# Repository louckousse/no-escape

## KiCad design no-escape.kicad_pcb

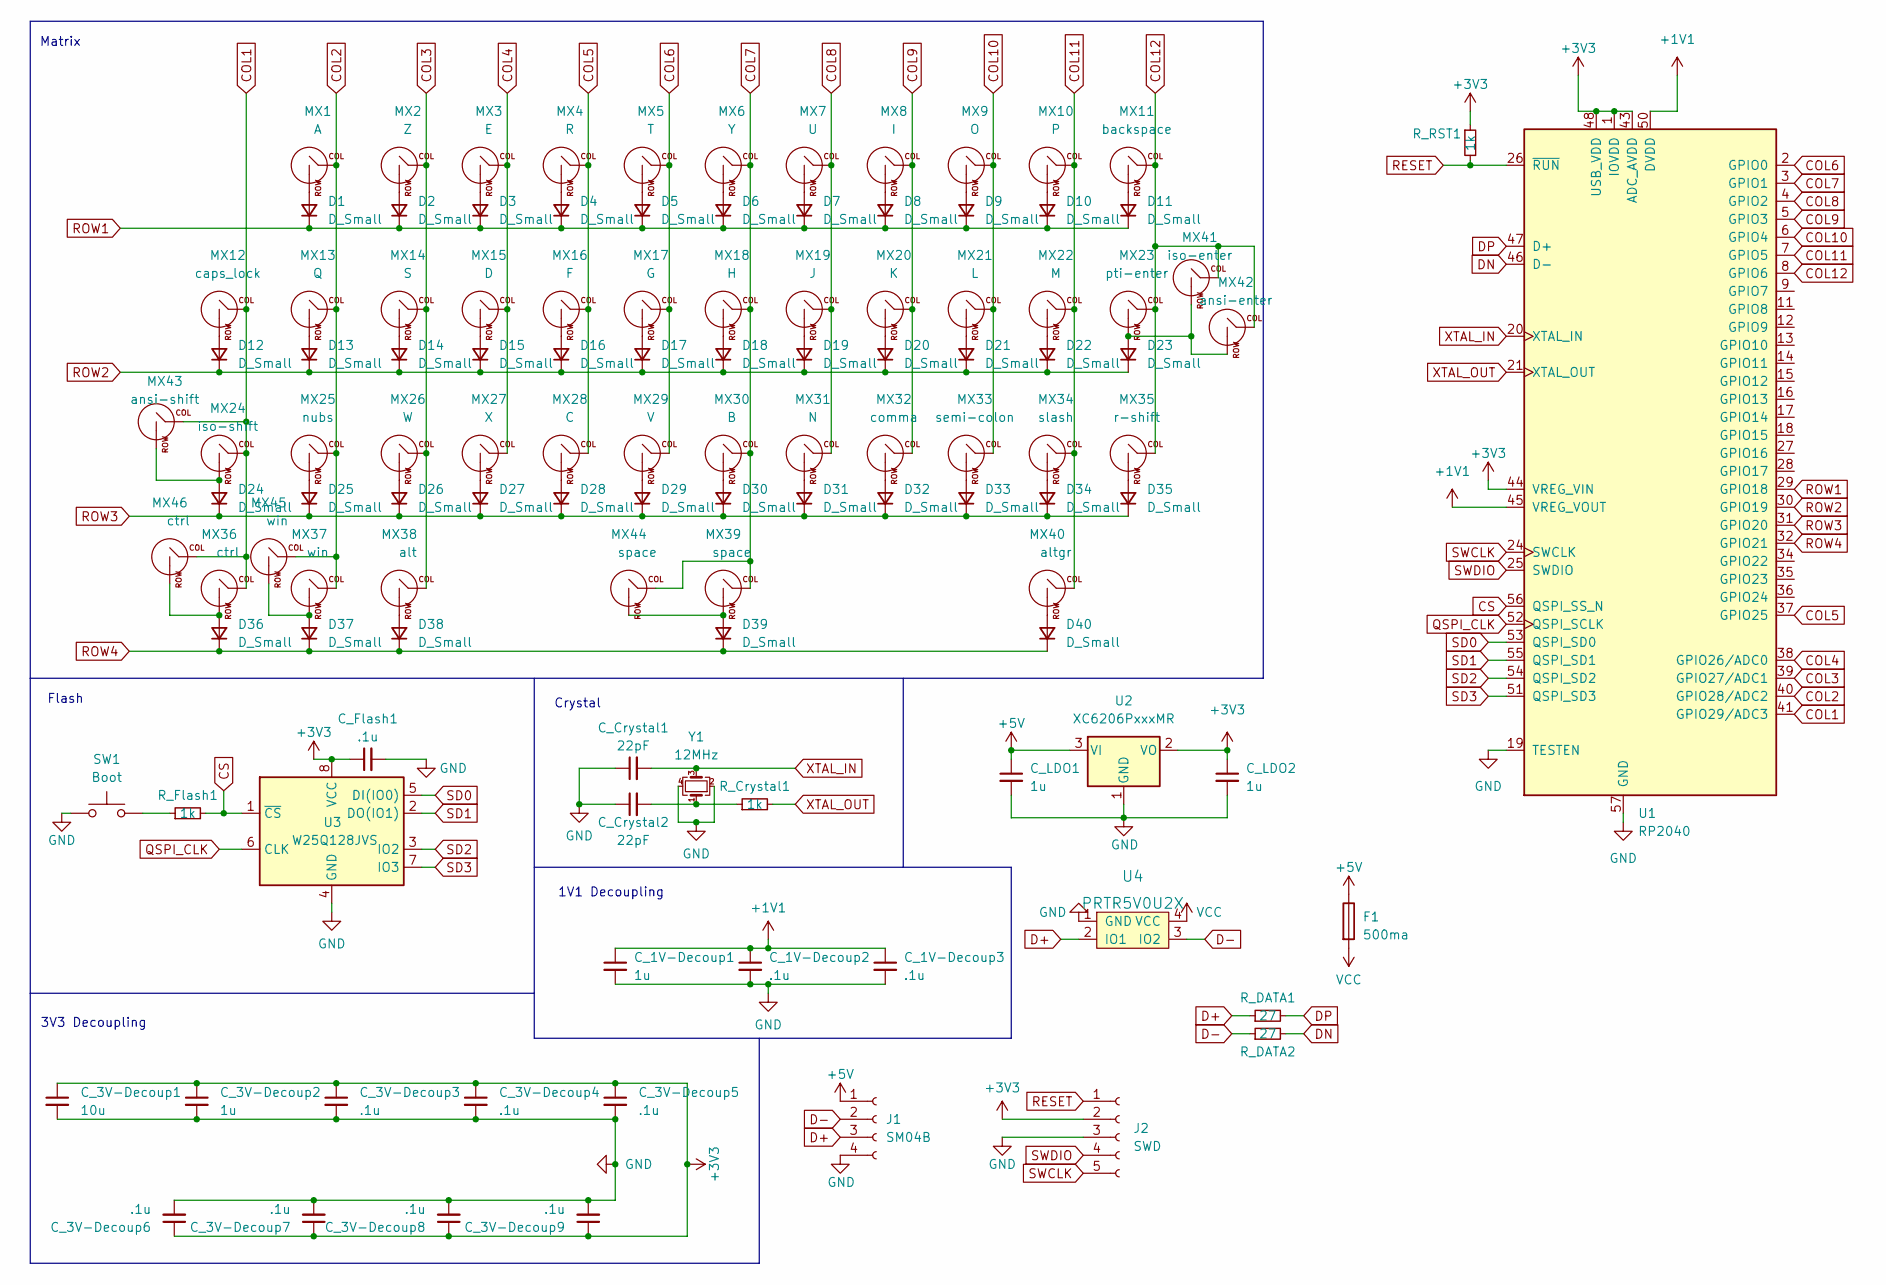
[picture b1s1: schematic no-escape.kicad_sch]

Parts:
C_1V-Decoup1, C_3V-Decoup2: 1u; C_0402_1005Metric
C_1V-Decoup2, C_1V-Decoup3, C_3V-Decoup3, C_3V-Decoup4, C_3V-Decoup5, C_3V-Decoup6, C_3V-Decoup7, C_3V-Decoup8, C_3V-Decoup9: .1u; C_0402_1005Metric
C_3V-Decoup1: 10u; C_0402_1005Metric
C_Crystal1, C_Crystal2: 22pF; C_0402_1005Metric
C_Flash1: .1u; C_0402_1005Metric
C_LDO1, C_LDO2: 1u; C_0402_1005Metric
D1, D2, D3, D4, D5, D6, D7, D8, D9, D10, D11, D12, D13, D14, D15, D16, D17, D18, D19, D20, D21, D22, D23, D24, D25, D26, D27, D28, D29, D30, D31, D32, D33, D34, D35, D36, D37, D38, D39, D40: D_Small; D_SOD-123
F1: 500ma; Fuse_0805_2012Metric
J1: SM04B; Molex_Pico-EZmate_78171-0004_1x04-1MP_P1.20mm_Vertical
J2: SWD; PinHeader_1x05_P2.54mm_Vertical
MX1: A; mx_1u
MX2: Z; mx_1u
MX3: E; mx_1u
MX4: R; mx_1u
MX5: T; mx_1u
MX6: Y; mx_1u
MX7: U; mx_1u
MX8: I; mx_1u
MX9: O; mx_1u
MX10: P; mx_1u
MX11: backspace; mx_15u
MX12: caps_lock; mx_stepped_caps
MX13: Q; mx_1u
MX14: S; mx_1u
MX15: D; mx_1u
MX16: F; mx_1u
MX17: G; mx_1u
MX18: H; mx_1u
MX19: J; mx_1u
MX20: K; mx_1u
MX21: L; mx_1u
MX22: M; mx_1u
MX23: pti-enter; mx_125u
MX24: iso-shift; mx_125u
MX25: nubs; mx_1u
MX26: W; mx_1u
MX27: X; mx_1u
MX28: C; mx_1u
MX29: V; mx_1u
MX30: B; mx_1u
MX31: N; mx_1u
MX32: comma; mx_1u
MX33: semi-colon; mx_1u
MX34: slash; mx_1u
MX35: r-shift; mx_175u
MX36: ctrl; mx_125u
MX37: win; mx_125u
MX38: alt; mx_1u
MX39: space; mx_7u
MX40: altgr; mx_1u
MX41: iso-enter; mx_iso
MX42: ansi-enter; mx_225u
MX43: ansi-shift; mx_225u
MX44: space; MX-Solderable-8U-ReversedStabilizers
MX45: win; mx_1u
MX46: ctrl; mx_15u
R_Crystal1: 1k; R_0402_1005Metric
R_DATA1, R_DATA2: 27; R_0402_1005Metric
R_Flash1: 1k; R_0402_1005Metric
R_RST1: 1k; R_0402_1005Metric
SW1: Boot; PinHeader_1x02_P2.54mm_Vertical
U1: RP2040; RP2040-QFN-56
U2: XC6206PxxxMR; SOT-23
U3: W25Q128JVS; SOIC-8_5.23x5.23mm_P1.27mm
U4: PRTR5V0U2X; SOT143B
Y1: 12MHz; Crystal_SMD_3225-4Pin_3.2x2.5mm

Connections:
+1V1: C_1V-Decoup1.1, C_1V-Decoup2.1, C_1V-Decoup3.1, U1.23 (DVDD), U1.45 (VREG_VOUT), U1.50 (DVDD)
+3V3: C_3V-Decoup1.1, C_3V-Decoup2.1, C_3V-Decoup3.1, C_3V-Decoup4.1, C_3V-Decoup5.1, C_3V-Decoup6.1, C_3V-Decoup7.1, C_3V-Decoup8.1, C_3V-Decoup9.1, C_Flash1.1, C_LDO2.1, J2.2, R_RST1.1, U1.1 (IOVDD), U1.10 (IOVDD), U1.22 (IOVDD), U1.33 (IOVDD), U1.42 (IOVDD), U1.43 (ADC_AVDD), U1.44 (VREG_VIN), U1.48 (USB_VDD), U1.49 (IOVDD), U2.2 (VO), U3.8 (VCC)
+5V: C_LDO1.1, F1.1, J1.1, U2.3 (VI)
COL1: MX12.1 (Passive), MX24.1 (Passive), MX36.1 (Passive), MX43.1 (Passive), MX46.1 (Passive), U1.41 (GPIO29/ADC3)
COL2: MX1.1 (Passive), MX13.1 (Passive), MX25.1 (Passive), MX37.1 (Passive), MX45.1 (Passive), U1.40 (GPIO28/ADC2)
COL3: MX2.1 (Passive), MX14.1 (Passive), MX26.1 (Passive), MX38.1 (Passive), U1.39 (GPIO27/ADC1)
COL4: MX3.1 (Passive), MX15.1 (Passive), MX27.1 (Passive), U1.38 (GPIO26/ADC0)
COL5: MX4.1 (Passive), MX16.1 (Passive), MX28.1 (Passive), U1.37 (GPIO25)
COL6: MX5.1 (Passive), MX17.1 (Passive), MX29.1 (Passive), U1.2 (GPIO0)
COL7: MX6.1 (Passive), MX18.1 (Passive), MX30.1 (Passive), MX39.1 (Passive), MX44.1 (Passive), U1.3 (GPIO1)
COL8: MX7.1 (Passive), MX19.1 (Passive), MX31.1 (Passive), U1.4 (GPIO2)
COL9: MX8.1 (Passive), MX20.1 (Passive), MX32.1 (Passive), U1.5 (GPIO3)
COL10: MX9.1 (Passive), MX21.1 (Passive), MX33.1 (Passive), U1.6 (GPIO4)
COL11: MX10.1 (Passive), MX22.1 (Passive), MX34.1 (Passive), MX40.1 (Passive), U1.7 (GPIO5)
COL12: MX11.1 (Passive), MX23.1 (Passive), MX35.1 (Passive), MX41.1 (Passive), MX42.1 (Passive), U1.8 (GPIO6)
CS: R_Flash1.2, U1.56 (QSPI_SS_N), U3.1 (~CS)
D+: J1.3, R_DATA1.1, U4.2 (IO1)
D-: J1.2, R_DATA2.1, U4.3 (IO2)
DN: R_DATA2.2, U1.46 (D-)
DP: R_DATA1.2, U1.47 (D+)
GND: C_1V-Decoup1.2, C_1V-Decoup2.2, C_1V-Decoup3.2, C_3V-Decoup1.2, C_3V-Decoup2.2, C_3V-Decoup3.2, C_3V-Decoup4.2, C_3V-Decoup5.2, C_3V-Decoup6.2, C_3V-Decoup7.2, C_3V-Decoup8.2, C_3V-Decoup9.2, C_Crystal1.1, C_Crystal2.1, C_Flash1.2, C_LDO1.2, C_LDO2.2, J1.4, J2.3, SW1.1, U1.19 (TESTEN), U1.57 (GND), U2.1 (GND), U3.4 (GND), U4.1 (GND), Y1.2, Y1.4
unnamed: C_Crystal2.2, R_Crystal1.1, Y1.1
unnamed: D1.2 (A), MX1.2 (ROW)
unnamed: D2.2 (A), MX2.2 (ROW)
unnamed: D3.2 (A), MX3.2 (ROW)
unnamed: D4.2 (A), MX4.2 (ROW)
unnamed: D5.2 (A), MX5.2 (ROW)
unnamed: D6.2 (A), MX6.2 (ROW)
unnamed: D7.2 (A), MX7.2 (ROW)
unnamed: D8.2 (A), MX8.2 (ROW)
unnamed: D9.2 (A), MX9.2 (ROW)
unnamed: D10.2 (A), MX10.2 (ROW)
unnamed: D11.2 (A), MX11.2 (ROW)
unnamed: D12.2 (A), MX12.2 (ROW)
unnamed: D13.2 (A), MX13.2 (ROW)
unnamed: D14.2 (A), MX14.2 (ROW)
unnamed: D15.2 (A), MX15.2 (ROW)
unnamed: D16.2 (A), MX16.2 (ROW)
unnamed: D17.2 (A), MX17.2 (ROW)
unnamed: D18.2 (A), MX18.2 (ROW)
unnamed: D19.2 (A), MX19.2 (ROW)
unnamed: D20.2 (A), MX20.2 (ROW)
unnamed: D21.2 (A), MX21.2 (ROW)
unnamed: D22.2 (A), MX22.2 (ROW)
unnamed: D23.2 (A), MX23.2 (ROW), MX41.2 (ROW), MX42.2 (ROW)
unnamed: D24.2 (A), MX24.2 (ROW), MX43.2 (ROW)
unnamed: D25.2 (A), MX25.2 (ROW)
unnamed: D26.2 (A), MX26.2 (ROW)
unnamed: D27.2 (A), MX27.2 (ROW)
unnamed: D28.2 (A), MX28.2 (ROW)
unnamed: D29.2 (A), MX29.2 (ROW)
unnamed: D30.2 (A), MX30.2 (ROW)
unnamed: D31.2 (A), MX31.2 (ROW)
unnamed: D32.2 (A), MX32.2 (ROW)
unnamed: D33.2 (A), MX33.2 (ROW)
unnamed: D34.2 (A), MX34.2 (ROW)
unnamed: D35.2 (A), MX35.2 (ROW)
unnamed: D36.2 (A), MX36.2 (ROW), MX46.2 (ROW)
unnamed: D37.2 (A), MX37.2 (ROW), MX45.2 (ROW)
unnamed: D38.2 (A), MX38.2 (ROW)
unnamed: D39.2 (A), MX39.2 (ROW), MX44.2 (ROW)
unnamed: D40.2 (A), MX40.2 (ROW)
unnamed: R_Flash1.1, SW1.2
QSPI_CLK: U1.52 (QSPI_SCLK), U3.6 (CLK)
RESET: J2.1, R_RST1.2, U1.26 (~RUN)
ROW1: D1.1 (K), D2.1 (K), D3.1 (K), D4.1 (K), D5.1 (K), D6.1 (K), D7.1 (K), D8.1 (K), D9.1 (K), D10.1 (K), D11.1 (K), U1.29 (GPIO18)
ROW2: D12.1 (K), D13.1 (K), D14.1 (K), D15.1 (K), D16.1 (K), D17.1 (K), D18.1 (K), D19.1 (K), D20.1 (K), D21.1 (K), D22.1 (K), D23.1 (K), U1.30 (GPIO19)
ROW3: D24.1 (K), D25.1 (K), D26.1 (K), D27.1 (K), D28.1 (K), D29.1 (K), D30.1 (K), D31.1 (K), D32.1 (K), D33.1 (K), D34.1 (K), D35.1 (K), U1.31 (GPIO20)
ROW4: D36.1 (K), D37.1 (K), D38.1 (K), D39.1 (K), D40.1 (K), U1.32 (GPIO21)
SD0: U1.53 (QSPI_SD0), U3.5 (DI(IO0))
SD1: U1.55 (QSPI_SD1), U3.2 (DO(IO1))
SD2: U1.54 (QSPI_SD2), U3.3 (IO2)
SD3: U1.51 (QSPI_SD3), U3.7 (IO3)
SWCLK: J2.5, U1.24 (SWCLK)
SWDIO: J2.4, U1.25 (SWDIO)
VCC: F1.2, U4.4 (VCC)
XTAL_IN: C_Crystal1.2, U1.20 (XTAL_IN), Y1.3
XTAL_OUT: R_Crystal1.2, U1.21 (XTAL_OUT)

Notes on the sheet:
Flash
1V1 Decoupling
Crystal
Matrix
3V3 Decoupling

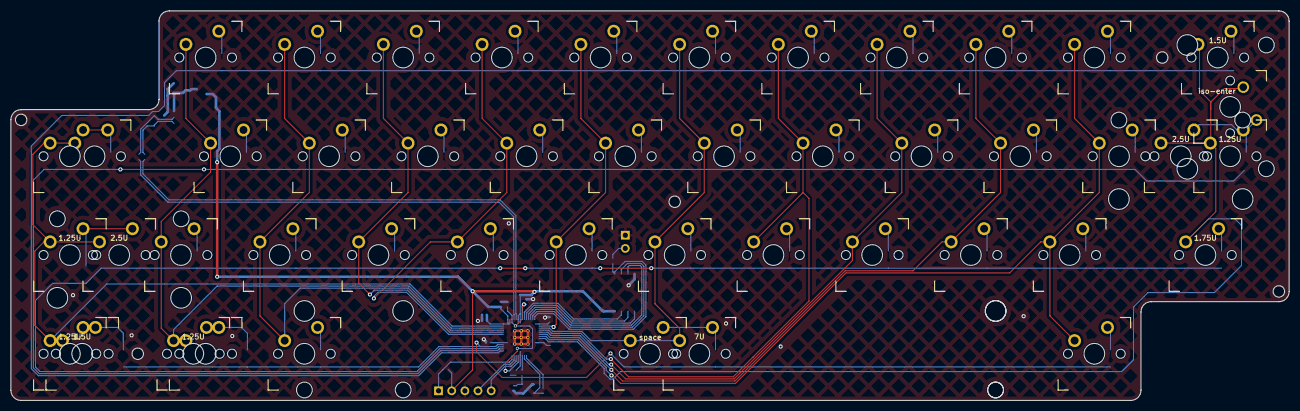
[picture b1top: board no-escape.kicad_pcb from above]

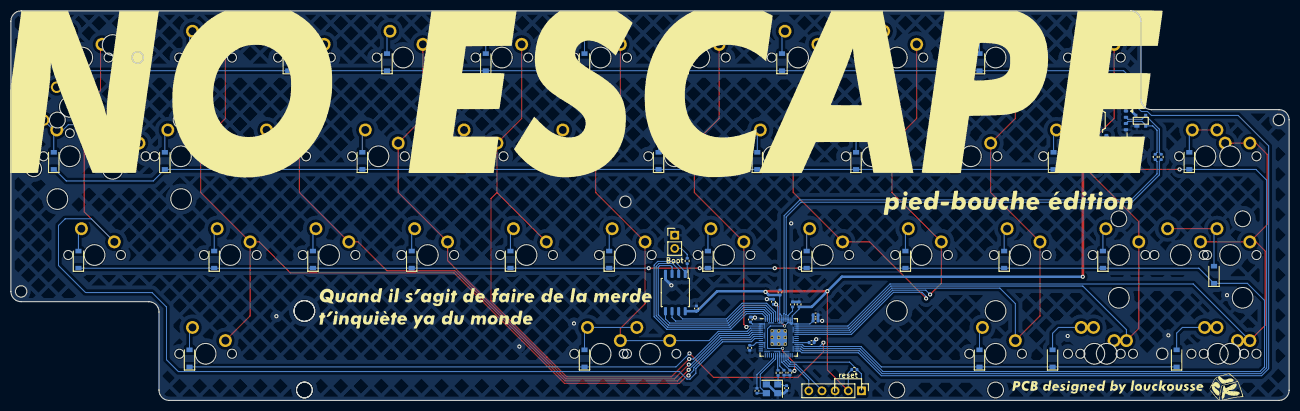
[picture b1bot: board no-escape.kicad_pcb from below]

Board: 2 copper layers, 246.6 x 75.1 mm, 117 parts (71 on the bottom side), 78 nets.

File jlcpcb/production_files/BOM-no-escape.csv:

Comment,Designator,Footprint,LCSC
1k,"R_Crystal1,R_Flash1,R_RST1",R_0402_1005Metric,C11702
PRTR5V0U2X,U4,SOT143B,C12333
.1u,"C_1V-Decoup2,C_1V-Decoup3,C_3V-Decoup3,C_3V-Decoup4,C_3V-Decoup5,C_3V-Decoup6,C_3V-Decoup7,C_3V-Decoup8,C_3V-Decoup9,C_Flash1",C_0402_1005Metric,C1525
10u,C_3V-Decoup1,C_0402_1005Metric,C15525
22pF,"C_Crystal1,C_Crystal2",C_0402_1005Metric,C1555
RP2040,U1,RP2040-QFN-56,C2040
27,"R_DATA1,R_DATA2",R_0402_1005Metric,C25100
SM04B,J1,Molex_Pico-EZmate_78171-0004_1x04-1MP_P1.20mm_Vertical,C528030
1u,"C_1V-Decoup1,C_3V-Decoup2,C_LDO1,C_LDO2",C_0402_1005Metric,C52923
XC6206PxxxMR,U2,SOT-23,C5446
D_Small,"D1,D10,D11,D12,D13,D14,D15,D16,D17,D18,D19,D2,D20,D21,D22,D23,D24,D25,D26,D27,D28,D29,D3,D30,D31,D32,D33,D34,D35,D36,D37,D38,D39,D4,D40,D5,D6,D7,D8,D9",D_SOD-123,C64898
500ma,F1,Fuse_0805_2012Metric,C883103
12MHz,Y1,Crystal_SMD_3225-4Pin_3.2x2.5mm,C9002
W25Q128JVS,U3,SOIC-8_5.23x5.23mm_P1.27mm,C97521
space,MX44,MX-Solderable-8U-ReversedStabilizers,
ansi-shift,MX43,mx_225u,
ansi-enter,MX42,mx_225u,
iso-enter,MX41,mx_iso,
pti-enter,MX23,mx_125u,
V,MX29,mx_1u,
space,MX39,mx_7u,
B,MX30,mx_1u,
win,MX37,mx_125u,
altgr,MX40,mx_1u,
U,MX7,mx_1u,
X,MX27,mx_1u,
G,MX17,mx_1u,
A,MX1,mx_1u,
D,MX15,mx_1u,
comma,MX32,mx_1u,
r-shift,MX35,mx_175u,
iso-shift,MX24,mx_125u,
Q,MX13,mx_1u,
O,MX9,mx_1u,
N,MX31,mx_1u,
S,MX14,mx_1u,
P,MX10,mx_1u,
K,MX20,mx_1u,
nubs,MX25,mx_1u,
M,MX22,mx_1u,
T,MX5,mx_1u,
ctrl,MX36,mx_125u,
H,MX18,mx_1u,
Y,MX6,mx_1u,
L,MX21,mx_1u,
F,MX16,mx_1u,
I,MX8,mx_1u,
backspace,MX11,mx_15u,
caps_lock,MX12,mx_stepped_caps,
E,MX3,mx_1u,
semi-colon,MX33,mx_1u,
slash,MX34,mx_1u,
R,MX4,mx_1u,
J,MX19,mx_1u,
C,MX28,mx_1u,
W,MX26,mx_1u,
alt,MX38,mx_1u,
Z,MX2,mx_1u,
SWD,J2,PinHeader_1x05_P2.54mm_Vertical,
Boot,SW1,PinHeader_1x02_P2.54mm_Vertical,
ctrl,MX46,mx_15u,
win,MX45,mx_1u,

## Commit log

2023-04-12 ready for prod
2023-04-14 add 1.5 1 bottom compatibility
2023-12-30 add Druz's review
2024-01-04 Silkscreen alignment, fixes
